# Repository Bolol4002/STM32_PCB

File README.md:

# STM32 PCB Design

Custom STM32 microcontroller board designed in KiCad. This project includes the schematic, PCB layout, and 3D render, with power integrity analysis covering decoupling capacitors and ferrite bead usage.

## Project Images

### Schematic

### PCB Layout

### 3D Render

---

# What is decoupling capacitors? 
A decoupling capacitor (or bypass capacitor) sits between the power supply pin ($V_{CC}$) and ground ($GND$) of an integrated circuit (IC) to isolate the chip from noise on the power rail and maintain stable operating voltage.

**Key Functions:**

* **Supplying Instantaneous Current:** When digital ICs switch states rapidly, they demand sudden bursts of current. Power supplies and long PCB traces cannot deliver current instantly due to trace inductance. The decoupling capacitor acts as a tiny, local energy reservoir, discharging immediately to prevent voltage dips (sags).
* **Filtering High-Frequency Noise:** Power supply lines act as antennas, picking up electromagnetic interference (EMI) and ripple. Because capacitive impedance decreases as frequency rises ($Z = \frac{1}{2\pi f C}$), high-frequency noise sees the capacitor as a short circuit and shunts safely to ground rather than entering the IC.
* **Preventing Inter-Component Crosstalk:** Noise generated by one switching IC can travel back into a shared power trace and disrupt neighboring components. Decoupling isolates (decouples) each component, keeping switching noise contained to its local loop.

**Operational Summary:**

| Circuit Condition | Capacitor Behavior | Impact on the IC |
| --- | --- | --- |
| **Steady DC Supply** | Blocks DC current (acts like an open circuit). | Normal power reaches the IC uninterrupted. |
| **High-Frequency AC Noise** | Offers low impedance to ground. | Shunts unwanted power noise away from sensitive pins. |
| **Transient Current Demand** | Rapidly discharges stored charge. | Keeps local supply voltage stable during logic transitions. |

**Placement & Sizing Guidelines:**

* **Physical Proximity:** Placement is critical. Decoupling capacitors must sit **as close as physically possible** to the IC's power and ground pins. Long traces introduce stray inductance, which degrades high-frequency performance.
* **Typical Capacitor Values:**
* **0.1 µF (Ceramic):** Standard choice for filtering high-frequency noise and fast switching spikes.
* **10 µF (Tantalum/Electrolytic):** Placed centrally as a "bulk" capacitor to smooth out lower-frequency, higher-energy voltage fluctuations across an entire circuit block.

---

# What is ferrite bead?
Assuming you mean a **ferrite bead**, it is a passive electronic component used to suppress and dissipate high-frequency electromagnetic noise in power supply lines and signal traces.

**Key Functions:**

* **Frequency-Selective Noise Dissipation:** At DC and low frequencies, a ferrite bead acts like a simple, low-resistance conductor, letting power or signals pass through unimpeded. At high frequencies (typically 10 MHz to over 1 GHz), its impedance spikes dramatically and it acts as a resistor, converting unwanted high-frequency noise energy into harmless heat.
* **Blocking EMI & RFI:** It prevents Electromagnetic Interference (EMI) and Radio Frequency Interference (RFI) from entering sensitive ICs or radiating outward into surrounding electronics.
* **Power Rail Isolation:** In mixed-signal designs, ferrite beads are placed inline on power traces to isolate noisy digital power rails from noise-sensitive analog power rails (such as audio, sensor, or RF sections).

**Ferrite Beads vs. Decoupling Capacitors:**

While decoupling capacitors and ferrite beads both fight high-frequency noise, they work in opposite ways and are often paired together:

| Component | Placement | Mechanism | Primary Job |
| --- | --- | --- | --- |
| **Decoupling Capacitor** | Parallel (Pin to Ground) | Shunts noise to ground ($Z \to 0$ at high frequencies). | Local energy storage & noise bypass. |
| **Ferrite Bead** | Series (Inline with Signal/Power) | Blocks noise inline and turns it into heat ($Z \to \text{high}$ at high frequencies). | High-frequency noise suppression & rail isolation. |

**Common Real-World Uses:**

* **L-Filters & Pi ($\pi$) Filters:** Combined with decoupling capacitors on both sides, a ferrite bead creates a multi-stage low-pass filter that provides near-total power supply isolation for sensitive chips.
* **Cable Chokes:** The thick plastic cylinder (clamshell choke) found near the end of laptop chargers or USB cables contains a ferrite core. It stops the cable from acting as an antenna that radiates high-frequency noise into the room.
* **Surface-Mount (SMD) Beads:** Tiny chip-sized ferrite beads soldered directly onto PCBs right before power enters high-speed microcontrollers or wireless modules.

---

# References

* [KiCad Documentation](https://docs.kicad.org/)
* [STMicroelectronics STM32 Documentation](https://www.st.com/en/microcontrollers-microprocessors/stm32-32-bit-arm-cortex-mcus.html)

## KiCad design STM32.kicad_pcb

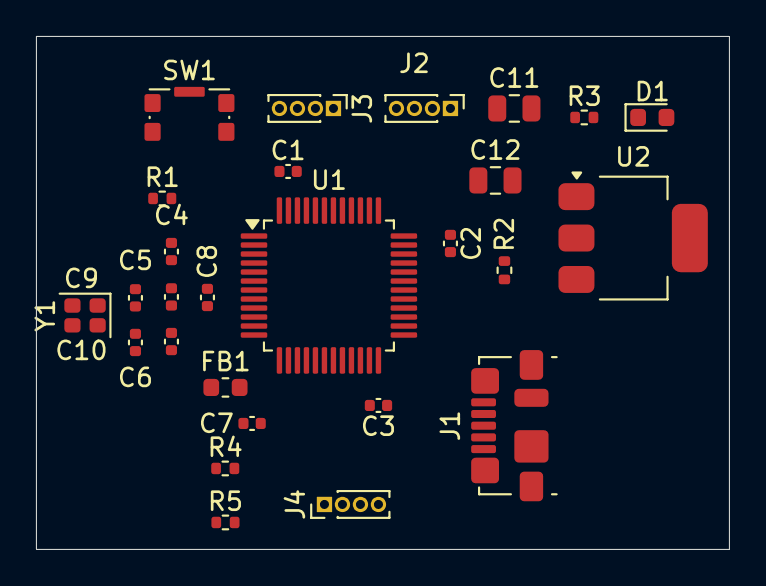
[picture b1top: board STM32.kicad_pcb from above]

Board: 2 copper layers, 38.5 x 28.5 mm, 27 parts (0 on the bottom side), 18 nets, no tracks yet.

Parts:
C1, C2, C3, C4, C8: 100n; C_0402_1005Metric
C5: 10n; C_0402_1005Metric
C6, C7: 1u; C_0402_1005Metric
C9, C10: 10p; C_0402_1005Metric
C11, C12: 22u; C_0805_2012Metric
D1: RED; LED_0603_1608Metric
FB1: 120R; L_0603_1608Metric
J1: USB_B_Micro; USB_Micro-B_Molex_47346-0001
J2, J3, J4: Conn_01x04_Pin; PinHeader_1x04_P1.00mm_Vertical
R1: 10K; R_0402_1005Metric
R2: 1k5; R_0402_1005Metric
R3, R4, R5: 1K5; R_0402_1005Metric
SW1: SW_SPDT; SW_SPST_CK_KMS2xxG
U1: STM32F103C8T6; LQFP-48_7x7mm_P0.5mm
U2: AMS1117-3.3; SOT-223-3_TabPin2
Y1: 16MHz; Crystal_SMD_2016-4Pin_2.0x1.6mm

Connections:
+3.3V: C1.1, C2.1, C3.1, C4.1, C7.1, C12.1, D1.2 (A), FB1.2, J2.1, J3.1, J4.1, R2.1, U1.1 (VBAT), U1.24 (VDD), U1.36 (VDD), U1.48 (VDD), U2.2 (VO)
+3.3VA: C5.1, C6.1, FB1.1, R4.1, R5.1, U1.9 (VDDA)
/BOOT0: R1.2, U1.44 (BOOT0)
/HSE_IN: C9.1, U1.5 (PD0), Y1.1
/HSE_OUT: C10.1, U1.6 (PD1), Y1.3
/I2C2_SCL: J4.2, R4.2, U1.21 (PB10)
/I2C2_SDA: J4.3, R5.2, U1.22 (PB11)
/NRST: C8.1, U1.7 (NRST)
/PWR_LED_K: D1.1 (K), R3.1
/SWCLK: J2.3, U1.37 (PA14)
/SWDIO: J2.2, U1.34 (PA13)
/SW_BOOT0: R1.1, SW1.2 (B)
/USART1_RX: J3.3, U1.43 (PB7)
/USART1_TX: J3.2, U1.42 (PB6)
/USB_D+: J1.3 (D+), R2.2, U1.33 (PA12)
/USB_D-: J1.2 (D-), U1.32 (PA11)
GND: C1.2, C2.2, C3.2, C4.2, C5.2, C6.2, C7.2, C8.2, C9.2, C10.2, C11.2, C12.2, J1.5 (GND), J2.4, J3.4, J4.4, R3.2, SW1.1 (A), U1.8 (VSSA), U1.23 (VSS), U1.35 (VSS), U1.47 (VSS), U2.1 (GND), Y1.2 (G), Y1.4 (G)
VBUS: C11.1, J1.1 (VBUS), U2.3 (VI)
